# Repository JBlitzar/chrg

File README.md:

# chrg

chrg is a usbc charging hub. You can use it to charge your devices! It uses a CH224K PD sink as input, and then 4xIP6518 PD source controllers as output. 

Thanks to the IP6518, it should support:

 - 45W
 - USB-C Power Delivery
 - BC1.2 charging
 - Qualcomm QC2.0 and 3.0 charging
 - Apple, Huawei, Samsung, and Spreadtrum fast charging protocols
   - I don't have any huawei phones, but maybe you do! You can use chrg to charge them.

 Of course, YMMV when plugging in multiple devices. It's mostly bottlenecked by the wattage of your upstream brick (or alternatively 45W as the ip6518 spec says).

 ### Why I made this project

 I made this project because I like doing USB projects, and after making a [USB *data* hub](https://github.com/jblitzar/uhub), I thought it would be cool to make a *charging* hub. Plus, this way I can plug in one brick and charge my phone and headphones at the same time. I also think it's cool and was a way to learn a new chip (IP6518).

## Schematic

Root schematic:

Schematic for the `out` block:

## PCB

[View on Kicanvas](https://kicanvas.org/?repo=https%3A%2F%2Fgithub.com%2FJBlitzar%2Fchrg%2Ftree%2Fmain%2FPCB%2Fchrg)

## CAD

[Onshape link](https://cad.onshape.com/documents/9567810a3a804626e0b9bd5e/w/546991992eff6807c34164d7/e/56ab2d679f572004bdd7b5fb?renderMode=0&uiState=6a89de2326941f564e9ba193)

Assembly: [CAD/chrg_assembly.step](CAD/chrg_assembly.step)

Or just check the [CAD folder](CAD/)

PCB is held in place with the mounting holes

## How to use

### Assembly

Print chrg_case.step instead and slide it in from the side, like so:

Then the pins should keep it secure. 

### Usage

Plug a usbc laptop charger into the side port. Then, charge your devices from the front ports!

## Testimonials

Don't just take it from me! Hear what users are saying about chrg

> *What are you making...*

> *this shit is not passing tsa bro*

> *Scary*

> *CHAAARGGGGEEEEEEE!!!!!!!!!!!!!!*

## BOM

|Item                                              |link                               |Cost|Notes           |
|--------------------------------------------------|-----------------------------------|----|----------------|
|5x PCB (moq)                                      |N/A                                |4   |JLC             |
|2x PCBA (moq)                                     |N/A                                |45.87|JLC             |
|JLC shipping + taxes                              |N/A                                |8   |                |
|1x case                                           |N/A                                |0   |I can print this myself|
|Total                                             |N/A                                |57.87|                |

### Fabrication BOM

Other fabrication outputs at [PCB/chrg/production](PCB/chrg/production)

|Designator                                        |Footprint                          |Quantity|Value           |LCSC Part #|Link|
|--------------------------------------------------|-----------------------------------|--------|----------------|-----------|----|
|C1                                                |C0603                              |1       |1uf             |C15849     |[link](https://www.lcsc.com/product-detail/C15849.html)|
|C10, C11, C12, C13, C2, C3, C4, C5, C6, C7, C8, C9|C0603                              |12      |22uF            |C59461     |[link](https://www.lcsc.com/product-detail/C59461.html)|
|C14                                               |C1206                              |1       |100uF           |C15008     |[link](https://www.lcsc.com/product-detail/C15008.html)|
|C32, C34, C39, C41, C46, C48, C53, C55            |C0402                              |8       |100nF           |C1525      |[link](https://www.lcsc.com/product-detail/C1525.html)|
|C33, C40, C47, C54                                |C0402                              |4       |1nF             |C1523      |[link](https://www.lcsc.com/product-detail/C1523.html)|
|F1                                                |FUSE-SMD_2410-T4A-125V             |1       |4A fuse         |C5220739   |[link](https://www.lcsc.com/product-detail/C5220739.html)|
|L1, L2, L3, L4                                    |IND-SMD_L14.4-W12.8                |4       |SLO1350H220MTT  |C364085    |[link](https://www.lcsc.com/product-detail/C364085.html)|
|LED1, LED6, LED7, LED8, LED9                      |LED0805-R-RD                       |5       |0805G           |C2297      |[link](https://www.lcsc.com/product-detail/C2297.html)|
|R16, R17, R19, R20, R21, R22, R23, R25, R26       |R0402                              |9       |3.3kΩ           |C25890     |[link](https://www.lcsc.com/product-detail/C25890.html)|
|R2                                                |R0402                              |1       |1k              |C11702     |[link](https://www.lcsc.com/product-detail/C11702.html)|
|R3, R4, R5, R6                                    |R0603                              |4       |2Ω              |C22977     |[link](https://www.lcsc.com/product-detail/C22977.html)|
|U1                                                |R0805                              |1       |10k             |C17414     |[link](https://www.lcsc.com/product-detail/C17414.html)|
|U11, U13, U15, U17                                |QFN-24_L4.0-W4.0-P0.50-BL-EP2.6    |4       |IP6518          |C181688    |[link](https://www.lcsc.com/product-detail/C181688.html)|
|U2                                                |ESSOP-10_L4.9-W3.9-P1.0-LS6.0-TL-EP|1       |CH224K          |C970725    |[link](https://www.lcsc.com/product-detail/C970725.html)|
|USB1, USB10, USB11, USB12, USB9                   |USB-C-SMD_TYPE-C-16PIN-2MD-073     |5       |TYPE-C 16PIN 2MD|C2765186   |[link](https://www.lcsc.com/product-detail/C2765186.html)|

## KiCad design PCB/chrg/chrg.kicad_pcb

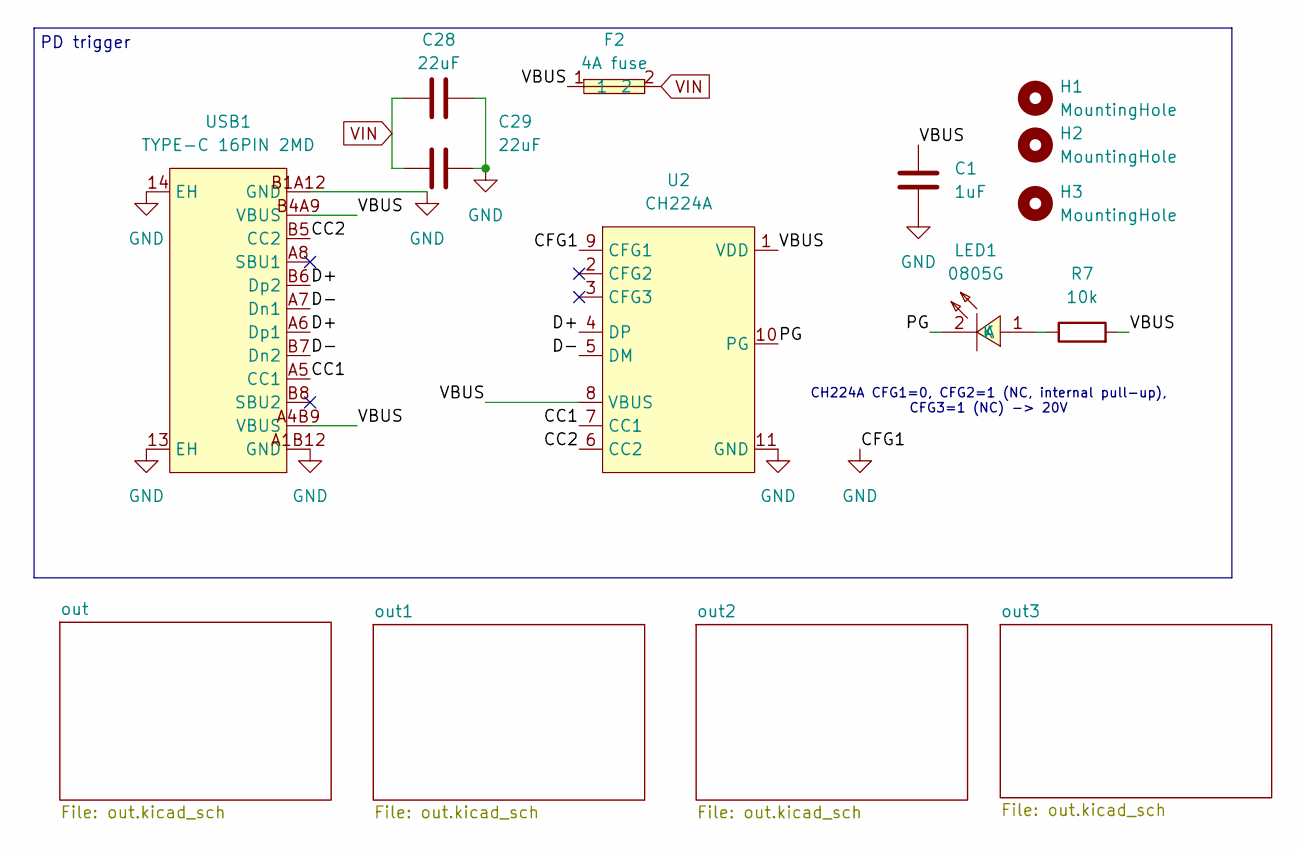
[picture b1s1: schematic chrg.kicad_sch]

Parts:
C1: 1uF; C_0603_1608Metric; MPN 2F01MC105X3M9D0; LCSC Part C54824972
C28, C29: 22uF; C_1210_3225Metric; MPN GMK325BJ226MM-P; LCSC Part C778721
F2: 4A fuse; F1206; MPN BSMD1206C-1400T; LCSC Part C41367227
H1, H2, H3: MountingHole; MountingHole_2.2mm_M2
LED1: 0805G; LED_0805_2012Metric; MPN KT-0805G; LCSC Part C2297
R7: 10k; R_0603_1608Metric; MPN RC0603FR-0710KL; LCSC Part C98220
U2: CH224A; SSOP-10-1EP_3.9x4.9mm_P1mm_EP2.1x3.3mm; MPN CH224A; LCSC Part C42459160
USB1: TYPE-C 16PIN 2MD; USB-C-SMD_TYPE-C-16PIN-2MD-073; MPN TYPE-C 16PIN 2MD(073); LCSC Part C2765186

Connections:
/CC1: U2.7 (CC1), USB1.A5 (CC1)
/CC2: U2.6 (CC2), USB1.B5 (CC2)
/D+: U2.4 (DP), USB1.A6 (Dp1), USB1.B6 (Dp2)
/D-: U2.5 (DM), USB1.A7 (Dn1), USB1.B7 (Dn2)
/PG: LED1.2 (K), U2.10 (PG)
/VBUS: C1.2, F2.1, R7.2, U2.1 (VDD), U2.8 (VBUS), USB1.A4B9 (VBUS), USB1.B4A9 (VBUS)
GND: C1.1, C28.1, C29.1, U2.9 (CFG1), U2.11 (GND), USB1.13 (EH), USB1.14 (EH), USB1.A1B12 (GND), USB1.B1A12 (GND); also elsewhere on the board
unnamed: LED1.1 (A), R7.1
VIN: C28.2, C29.2, F2.2; also elsewhere on the board

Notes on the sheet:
PD trigger
CH224A CFG1=0, CFG2=1 (NC, internal pull-up), CFG3=1 (NC) -> 20V

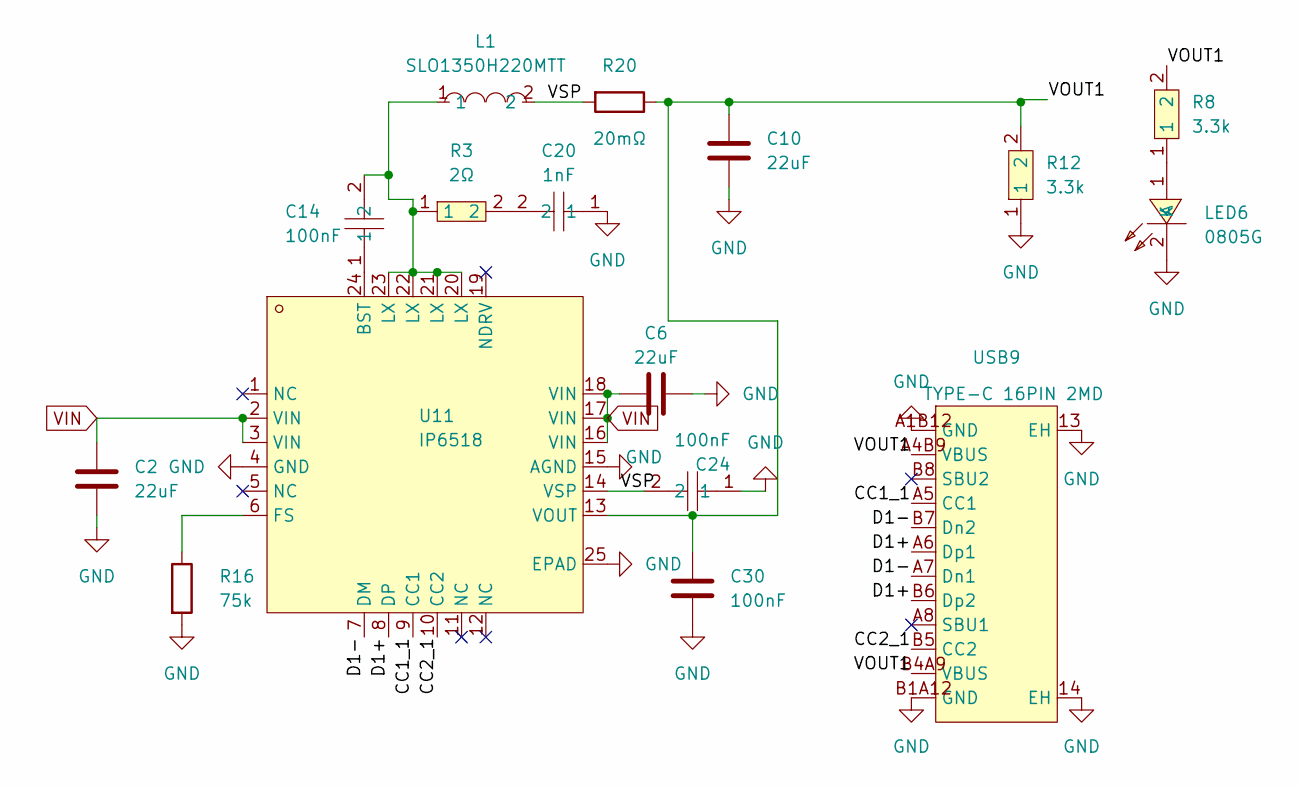
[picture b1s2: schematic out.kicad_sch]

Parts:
C2, C6, C10: 22uF; C_1210_3225Metric; MPN GMK325BJ226MM-P; LCSC Part C778721
C14, C24, C30: 100nF; C_0603_1608Metric; MPN CGA0603X7R104M500JT; LCSC Part C52711259
C20: 1nF; C_0603_1608Metric; MPN CC0603FRNPO9BN102; LCSC Part C309468
L1: SLO1350H220MTT; IND-SMD_L14.4-W12.8; MPN SLO1350H220MTT; LCSC Part C364085
LED6: 0805G; LED_0805_2012Metric; MPN KT-0805G; LCSC Part C2297
R3: 2Ω; R_0603_1608Metric; MPN 0603WAF200KT5E; LCSC Part C22977
R8, R12: 3.3k; R_0603_1608Metric; MPN FRC0603F3301TS; LCSC Part C2907023
R16: 75k; R_0603_1608Metric; MPN 0603WAF7502T5E; LCSC Part C23242
R20: 20mΩ; R_1206_3216Metric; MPN FRM121WFR020TM; LCSC Part C7420010
U11: IP6518; QFN-24-1EP_4x4mm_P0.5mm_EP2.6x2.6mm; MPN IP6518; LCSC Part C181688
USB9: TYPE-C 16PIN 2MD; USB-C-SMD_TYPE-C-16PIN-2MD-073; MPN TYPE-C 16PIN 2MD(073); LCSC Part C2765186

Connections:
/out/CC1_1: U11.9 (CC1), USB9.A5 (CC1)
/out/CC2_1: U11.10 (CC2), USB9.B5 (CC2)
/out/D1+: U11.8 (DP), USB9.A6 (Dp1), USB9.B6 (Dp2)
/out/D1-: U11.7 (DM), USB9.A7 (Dn1), USB9.B7 (Dn2)
/out/VOUT1: C10.2, C30.1, R8.2, R12.2, R20.1, U11.13 (VOUT), USB9.A4B9 (VBUS), USB9.B4A9 (VBUS)
/out/VSP: C24.2, L1.2, R20.2, U11.14 (VSP)
GND: C2.1, C6.2, C10.1, C20.1, C24.1, C30.2, LED6.2 (K), R12.1, R16.2, U11.4 (GND), U11.15 (AGND), U11.25 (EPAD), USB9.13 (EH), USB9.14 (EH), USB9.A1B12 (GND), USB9.B1A12 (GND); also elsewhere on the board
unnamed: C14.2, L1.1, R3.1, U11.20 (LX), U11.21 (LX), U11.22 (LX), U11.23 (LX)
unnamed: C20.2, R3.2
unnamed: LED6.1 (A), R8.1
unnamed: C14.1, U11.24 (BST)
unnamed: R16.1, U11.6 (FS)
VIN: C2.2, C6.1, U11.2 (VIN), U11.3 (VIN), U11.16 (VIN), U11.17 (VIN), U11.18 (VIN); also elsewhere on the board

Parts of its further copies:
C3, C4, C5, C7, C8, C9, C11, C12, C13: 22uF; C_1210_3225Metric; MPN GMK325BJ226MM-P; LCSC Part C778721
C17, C18, C19, C25, C26, C27, C31, C32, C33: 100nF; C_0603_1608Metric; MPN CGA0603X7R104M500JT; LCSC Part C52711259
C21, C22, C23: 1nF; C_0603_1608Metric; MPN CC0603FRNPO9BN102; LCSC Part C309468
L2, L3, L4: SLO1350H220MTT; IND-SMD_L14.4-W12.8; MPN SLO1350H220MTT; LCSC Part C364085
LED7, LED8, LED9: 0805G; LED_0805_2012Metric; MPN KT-0805G; LCSC Part C2297
R4, R5, R6: 2Ω; R_0603_1608Metric; MPN 0603WAF200KT5E; LCSC Part C22977
R9, R10, R11, R13, R14, R15: 3.3k; R_0603_1608Metric; MPN FRC0603F3301TS; LCSC Part C2907023
R17, R18, R19: 75k; R_0603_1608Metric; MPN 0603WAF7502T5E; LCSC Part C23242
R21, R22, R23: 20mΩ; R_1206_3216Metric; MPN FRM121WFR020TM; LCSC Part C7420010
U13, U15, U17: IP6518; QFN-24-1EP_4x4mm_P0.5mm_EP2.6x2.6mm; MPN IP6518; LCSC Part C181688
USB10, USB11, USB12: TYPE-C 16PIN 2MD; USB-C-SMD_TYPE-C-16PIN-2MD-073; MPN TYPE-C 16PIN 2MD(073); LCSC Part C2765186

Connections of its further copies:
/out1/CC1_1: U13.9 (CC1), USB10.A5 (CC1)
/out1/CC2_1: U13.10 (CC2), USB10.B5 (CC2)
/out1/D1+: U13.8 (DP), USB10.A6 (Dp1), USB10.B6 (Dp2)
/out1/D1-: U13.7 (DM), USB10.A7 (Dn1), USB10.B7 (Dn2)
/out1/VOUT1: C11.2, C31.1, R9.2, R13.2, R21.1, U13.13 (VOUT), USB10.A4B9 (VBUS), USB10.B4A9 (VBUS)
/out1/VSP: C25.2, L2.2, R21.2, U13.14 (VSP)
/out2/CC1_1: U15.9 (CC1), USB11.A5 (CC1)
/out2/CC2_1: U15.10 (CC2), USB11.B5 (CC2)
/out2/D1+: U15.8 (DP), USB11.A6 (Dp1), USB11.B6 (Dp2)
/out2/D1-: U15.7 (DM), USB11.A7 (Dn1), USB11.B7 (Dn2)
/out2/VOUT1: C12.2, C32.1, R10.2, R14.2, R22.1, U15.13 (VOUT), USB11.A4B9 (VBUS), USB11.B4A9 (VBUS)
/out2/VSP: C26.2, L3.2, R22.2, U15.14 (VSP)
/out3/CC1_1: U17.9 (CC1), USB12.A5 (CC1)
/out3/CC2_1: U17.10 (CC2), USB12.B5 (CC2)
/out3/D1+: U17.8 (DP), USB12.A6 (Dp1), USB12.B6 (Dp2)
/out3/D1-: U17.7 (DM), USB12.A7 (Dn1), USB12.B7 (Dn2)
/out3/VOUT1: C13.2, C33.1, R11.2, R15.2, R23.1, U17.13 (VOUT), USB12.A4B9 (VBUS), USB12.B4A9 (VBUS)
/out3/VSP: C27.2, L4.2, R23.2, U17.14 (VSP)
GND: C3.1, C4.1, C5.1, C7.2, C8.2, C9.2, C11.1, C12.1, C13.1, C21.1, C22.1, C23.1, C25.1, C26.1, C27.1, C31.2, C32.2, C33.2, LED7.2 (K), LED8.2 (K), LED9.2 (K), R13.1, R14.1, R15.1, R17.2, R18.2, R19.2, U13.4 (GND), U13.15 (AGND), U13.25 (EPAD), U15.4 (GND), U15.15 (AGND), U15.25 (EPAD), U17.4 (GND), U17.15 (AGND), U17.25 (EPAD), USB10.13 (EH), USB10.14 (EH), USB10.A1B12 (GND), USB10.B1A12 (GND), USB11.13 (EH), USB11.14 (EH), USB11.A1B12 (GND), USB11.B1A12 (GND), USB12.13 (EH), USB12.14 (EH), USB12.A1B12 (GND), USB12.B1A12 (GND); also elsewhere on the board
unnamed: C17.2, L2.1, R4.1, U13.20 (LX), U13.21 (LX), U13.22 (LX), U13.23 (LX)
unnamed: C18.2, L3.1, R5.1, U15.20 (LX), U15.21 (LX), U15.22 (LX), U15.23 (LX)
unnamed: C19.2, L4.1, R6.1, U17.20 (LX), U17.21 (LX), U17.22 (LX), U17.23 (LX)
unnamed: C21.2, R4.2
unnamed: C22.2, R5.2
unnamed: C23.2, R6.2
unnamed: LED7.1 (A), R9.1
unnamed: LED8.1 (A), R10.1
unnamed: LED9.1 (A), R11.1
unnamed: C17.1, U13.24 (BST)
unnamed: R17.1, U13.6 (FS)
unnamed: C18.1, U15.24 (BST)
unnamed: R18.1, U15.6 (FS)
unnamed: C19.1, U17.24 (BST)
unnamed: R19.1, U17.6 (FS)
VIN: C3.2, C4.2, C5.2, C7.1, C8.1, C9.1, U13.2 (VIN), U13.3 (VIN), U13.16 (VIN), U13.17 (VIN), U13.18 (VIN), U15.2 (VIN), U15.3 (VIN), U15.16 (VIN), U15.17 (VIN), U15.18 (VIN), U17.2 (VIN), U17.3 (VIN), U17.16 (VIN), U17.17 (VIN), U17.18 (VIN); also elsewhere on the board

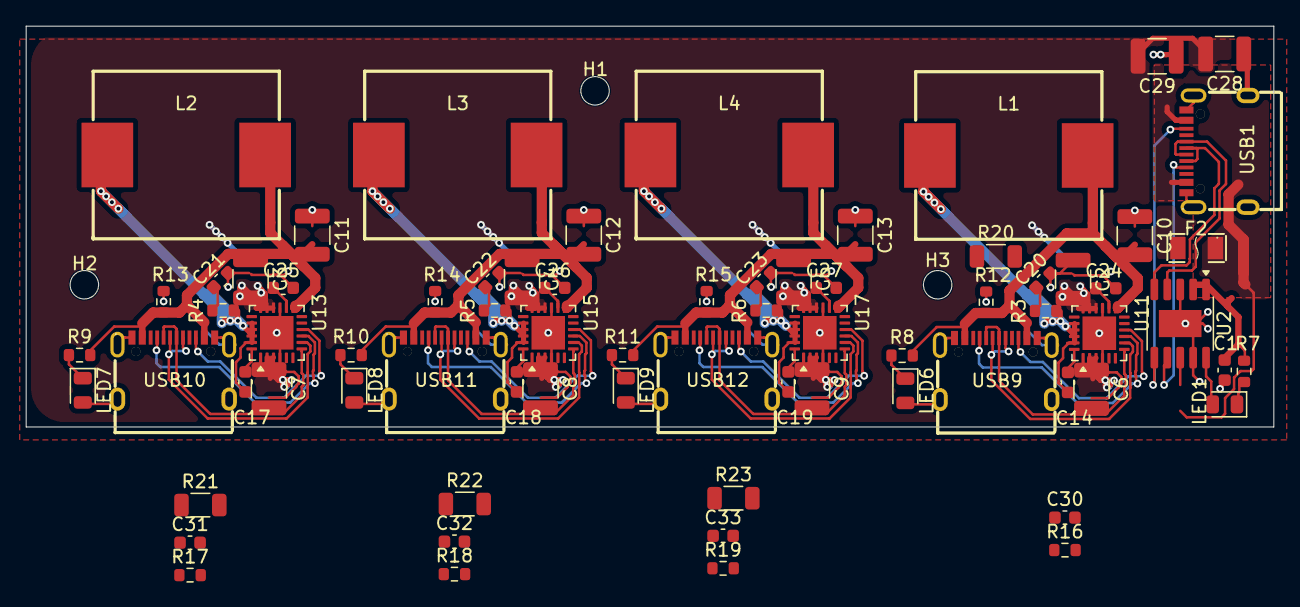
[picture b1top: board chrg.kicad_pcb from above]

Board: 2 copper layers, 96.5 x 31.0 mm, 76 parts (1 on the bottom side), 53 nets.

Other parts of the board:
kobee-studio-6A88F8E8: Kobee Studio; kobee-studio-6A88F8A7

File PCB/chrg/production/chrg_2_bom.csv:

Designator,Footprint,Quantity,Value,LCSC Part #
C1,0603,1,1uf,C29936
"C10, C11, C12, C13, C2, C3, C4, C5, C6, C7, C8, C9",0603,12,22uF,C59461
"C14, C17, C18, C19, C24, C25, C26, C27",0603,8,100nF,C52711259
"C20, C21, C22, C23",0603,4,1nF,C309468
"C28, C29",1206,2,47uF,C6119973
F2,F1206,1,4A fuse,C41367227
"L1, L2, L3, L4",IND-SMD_L14.4-W12.8,4,SLO1350H220MTT,C364085
"LED1, LED6, LED7, LED8, LED9",0805,5,0805G,C2297
R1,0603,1,1k,C22548
"R10, R11, R12, R13, R14, R15, R7, R8, R9",0603,9,3.3k,C2907023
R2,0603,1,10k,C98220
"R3, R4, R5, R6",0603,4,2Ω,C22977
"U11, U13, U15, U17",QFN-24-1EP_4x4mm_P0.5mm_EP2.6x2.6mm,4,IP6518,C181688
U2,SSOP-10-1EP_3.9x4.9mm_P1mm_EP2.1x3.3mm,1,CH224A,C42459160
"USB1, USB10, USB11, USB12, USB9",USB-C-SMD_TYPE-C-16PIN-2MD-073,5,TYPE-C 16PIN 2MD,C2765186
